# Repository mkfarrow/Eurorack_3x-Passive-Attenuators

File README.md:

# Eurorack_3x-Passive-Attenuators

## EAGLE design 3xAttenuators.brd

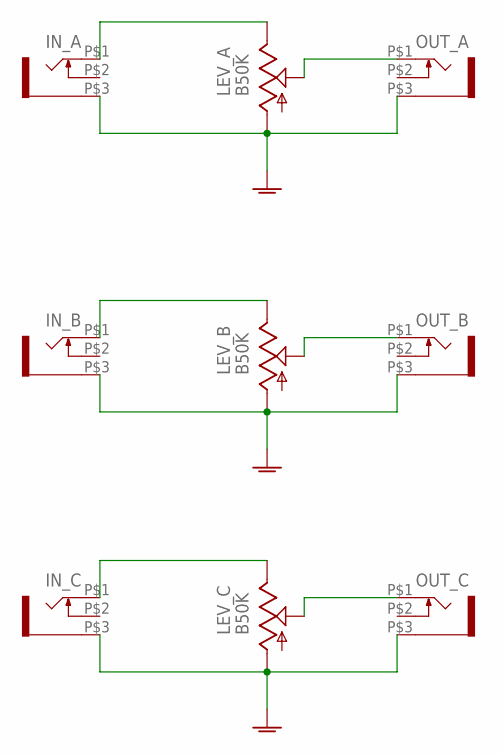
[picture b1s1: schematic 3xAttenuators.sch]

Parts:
IN_A: THONKICONN_WQP-PJ301M-12_JACK
IN_B: THONKICONN_WQP-PJ301M-12_JACK
IN_C: THONKICONN_WQP-PJ301M-12_JACK
LEV_A: B50K; MUSICTHINGMODULAR_9MM_SNAP-IN_POT
LEV_B: B50K; MUSICTHINGMODULAR_9MM_SNAP-IN_POT
LEV_C: B50K; MUSICTHINGMODULAR_9MM_SNAP-IN_POT
OUT_A: THONKICONN_WQP-PJ301M-12_JACK
OUT_B: THONKICONN_WQP-PJ301M-12_JACK
OUT_C: THONKICONN_WQP-PJ301M-12_JACK

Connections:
GND: IN_A.P$3 (1), IN_B.P$3 (1), IN_C.P$3 (1), LEV_A.1 (A), LEV_B.1 (A), LEV_C.1 (A), OUT_A.P$3 (1), OUT_B.P$3 (1), OUT_C.P$3 (1)
unnamed: IN_C.P$1 (2), LEV_C.3 (E)
unnamed: LEV_A.2 (S), OUT_A.P$1 (2)
unnamed: IN_B.P$1 (2), LEV_B.3 (E)
unnamed: LEV_B.2 (S), OUT_B.P$1 (2)
unnamed: IN_A.P$1 (2), LEV_A.3 (E)
unnamed: LEV_C.2 (S), OUT_C.P$1 (2)

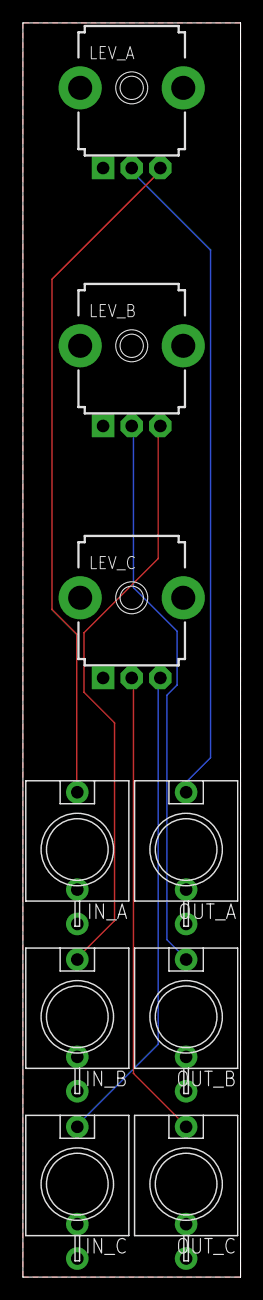
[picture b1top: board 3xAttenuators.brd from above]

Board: 2 copper layers, 19.0 x 109.5 mm, 9 parts (0 on the bottom side), 7 nets.

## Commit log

2022-06-10 adding cad files
2022-06-10 add schematic
2022-12-21 adding rendered images of pcbs
2022-12-22 cropped images
